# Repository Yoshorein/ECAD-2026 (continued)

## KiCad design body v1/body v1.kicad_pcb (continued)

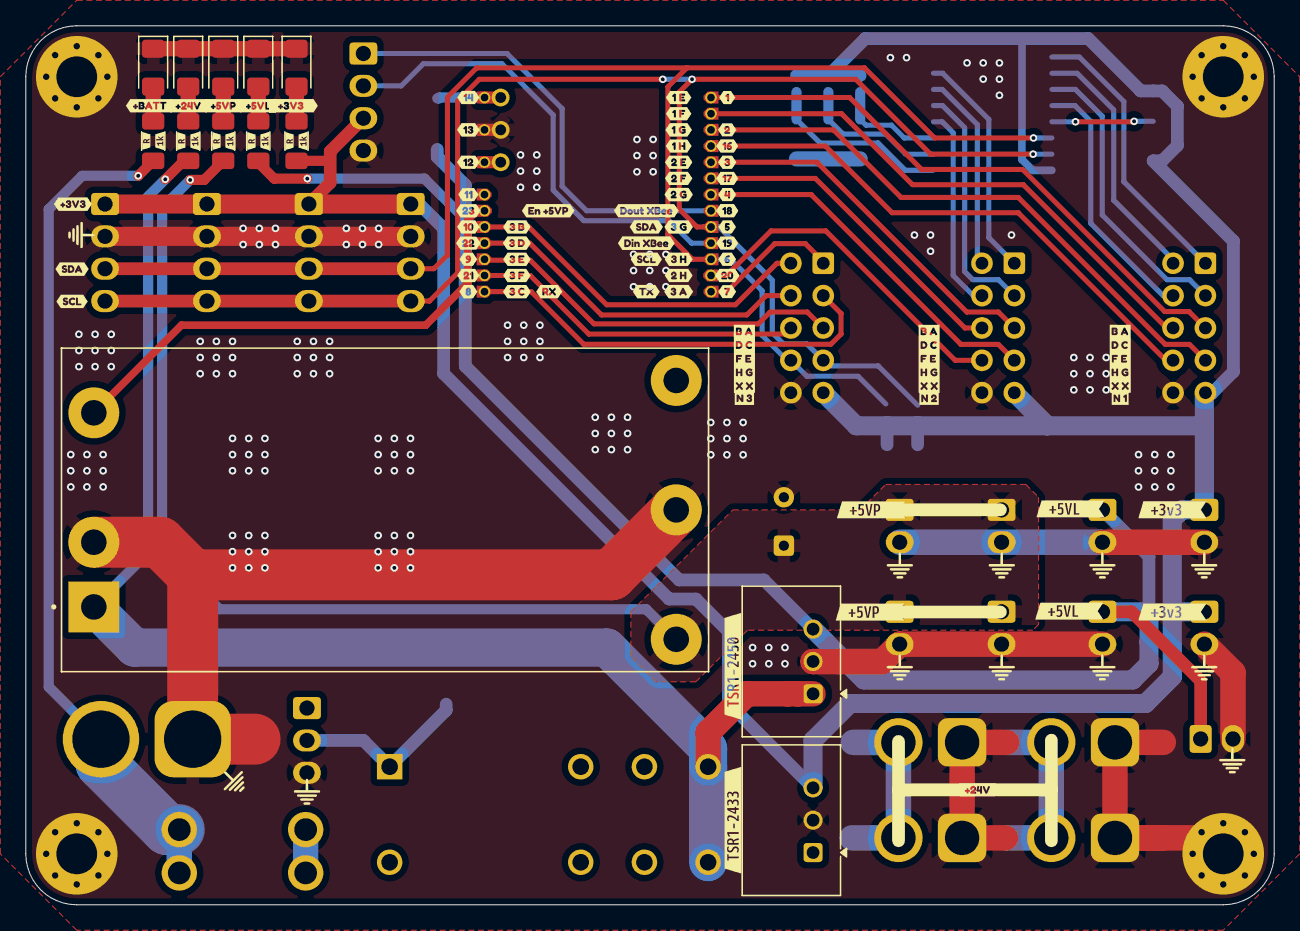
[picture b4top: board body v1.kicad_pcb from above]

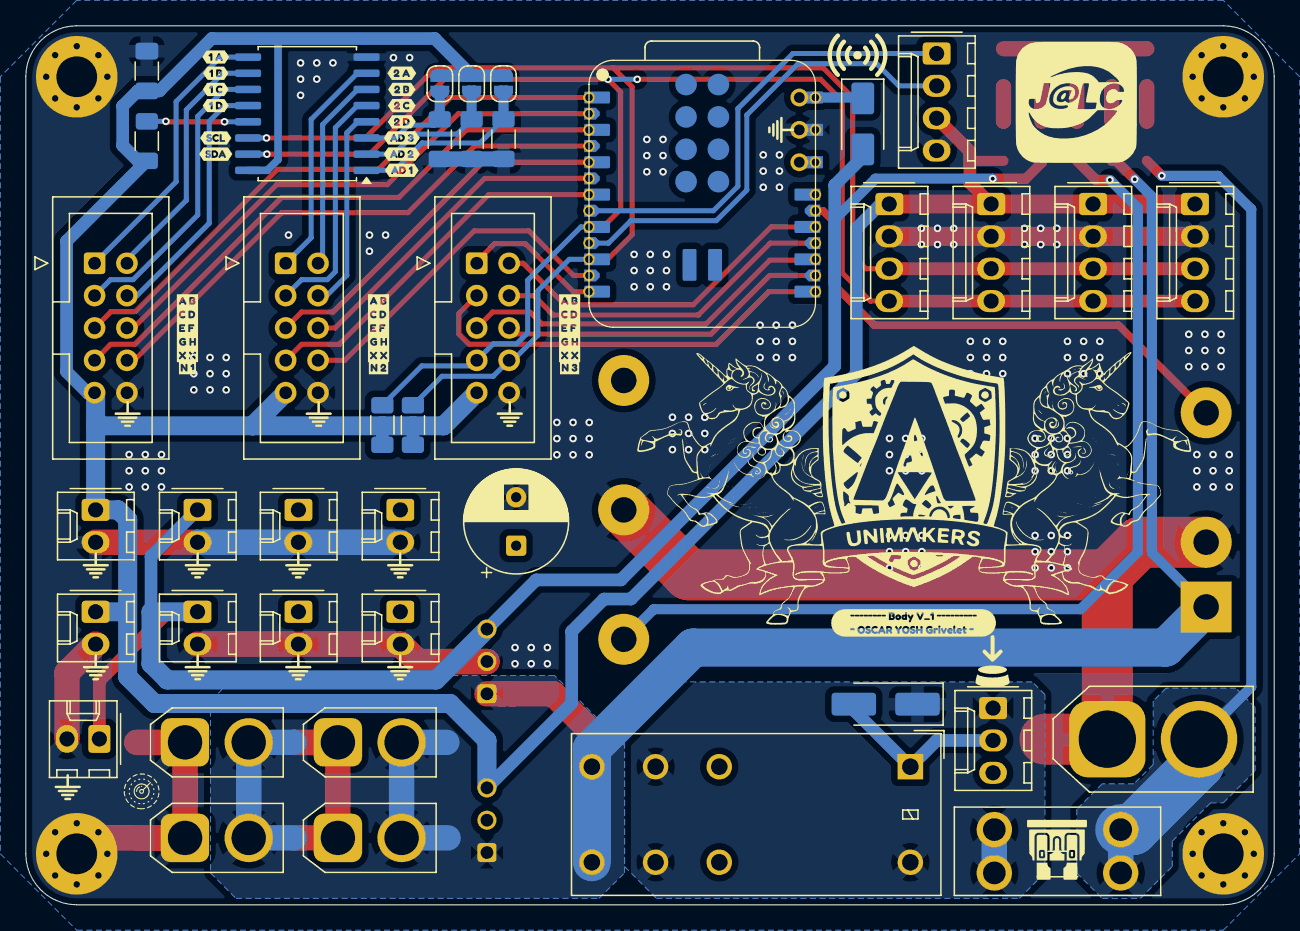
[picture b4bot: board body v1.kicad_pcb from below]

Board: 2 copper layers, 98.0 x 69.0 mm, 155 parts (60 on the bottom side), 45 nets.

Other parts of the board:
kibuzzard-69B7FC1F: G***; kibuzzard-69B7FC1F
kibuzzard-69B7FC2C: G***; kibuzzard-69B7FC2C
kibuzzard-69B7FC3A: G***; kibuzzard-69B7FC3A
kibuzzard-69B7FC3F: G***; kibuzzard-69B7FC3F
kibuzzard-69B7FC4C: G***; kibuzzard-69B7FC4C
kibuzzard-69B7FC5D: G***; kibuzzard-69B7FC5D
kibuzzard-69B7FC6B: G***; kibuzzard-69B7FC6B
kibuzzard-69B7FC8A: G***; kibuzzard-69B7FC8A
kibuzzard-69B7FC8F: G***; kibuzzard-69B7FC8F
kibuzzard-69B7FC9A: G***; kibuzzard-69B7FC9A
kibuzzard-69B7FC16: G***; kibuzzard-69B7FC16
kibuzzard-69B7FC28: G***; kibuzzard-69B7FC28
kibuzzard-69B7FC30: G***; kibuzzard-69B7FC30
kibuzzard-69B7FC34: G***; kibuzzard-69B7FC34
kibuzzard-69B7FC45: G***; kibuzzard-69B7FC45
kibuzzard-69B7FC49: G***; kibuzzard-69B7FC49
kibuzzard-69B7FC50: G***; kibuzzard-69B7FC50
kibuzzard-69B7FC58: G***; kibuzzard-69B7FC58
kibuzzard-69B7FC64: G***; kibuzzard-69B7FC64
kibuzzard-69B7FC71: G***; kibuzzard-69B7FC71
kibuzzard-69B7FC84: G***; kibuzzard-69B7FC84
kibuzzard-69B7FC95: G***; kibuzzard-69B7FC95
kibuzzard-69B7FF7A: G***; kibuzzard-69B7FF7A
kibuzzard-69B7FF72: G***; kibuzzard-69B7FF72
kibuzzard-69B7FFCA: G***; kibuzzard-69B7FFCA
kibuzzard-69B800EA, kibuzzard-69B800EA#2: G***; kibuzzard-69B800EA
kibuzzard-69B80110, kibuzzard-69B80110#2: G***; kibuzzard-69B80110
kibuzzard-69B80117, kibuzzard-69B80117#2: G***; kibuzzard-69B80117
kibuzzard-69BAE0CF: G***; kibuzzard-69BAE0CF
kibuzzard-69BAE4CB: G***; kibuzzard-69BAE4CB
kibuzzard-69BAE4D9: G***; kibuzzard-69BAE4D9
kibuzzard-69BAE4E7: G***; kibuzzard-69BAE4E7
kibuzzard-69BAE4F1: G***; kibuzzard-69BAE4F1
kibuzzard-69BAE7DC: G***; kibuzzard-69BAE7DC
kibuzzard-69BAE8DD, kibuzzard-69BAE8DD#2, kibuzzard-69BAE8DD#3: G***; kibuzzard-69BAE8DD
kibuzzard-69BAE35E: G***; kibuzzard-69BAE35E
kibuzzard-69BAE38F: G***; kibuzzard-69BAE38F
kibuzzard-69BAE48B: G***; kibuzzard-69BAE48B
kibuzzard-69BAE75D, kibuzzard-69BAE75D#2, kibuzzard-69BAE75D#3: G***; kibuzzard-69BAE75D
kibuzzard-69BAE77A: G***; kibuzzard-69BAE77A
kibuzzard-69BAE350: G***; kibuzzard-69BAE350
kibuzzard-69BAE367: G***; kibuzzard-69BAE367
kibuzzard-69BAE380: G***; kibuzzard-69BAE380
kibuzzard-69BAE387: G***; kibuzzard-69BAE387
kibuzzard-69BAE395: G***; kibuzzard-69BAE395
kibuzzard-69BAE431: G***; kibuzzard-69BAE431
kibuzzard-69BAE443: G***; kibuzzard-69BAE443
kibuzzard-69BAE476: G***; kibuzzard-69BAE476
kibuzzard-69BAE766, kibuzzard-69BAE766#2, kibuzzard-69BAE766#3: G***; kibuzzard-69BAE766
kibuzzard-69BAE772: G***; kibuzzard-69BAE772
kibuzzard-69BAE799: G***; kibuzzard-69BAE799
kibuzzard-69BAE836: G***; kibuzzard-69BAE836
kibuzzard-69BAED5C: G***; kibuzzard-69BAED5C
kibuzzard-69BAED6C: G***; kibuzzard-69BAED6C
kibuzzard-69BAED73: G***; kibuzzard-69BAED73
kibuzzard-69BAED80: G***; kibuzzard-69BAED80
kibuzzard-69BAEDC3: G***; kibuzzard-69BAEDC3
kibuzzard-69BAEDD0: G***; kibuzzard-69BAEDD0
kibuzzard-69BAEDD6: G***; kibuzzard-69BAEDD6
kibuzzard-69BAEDDC: G***; kibuzzard-69BAEDDC
kibuzzard-69BAEEA0: G***; kibuzzard-69BAEEA0
kibuzzard-69BAEEAC: G***; kibuzzard-69BAEEAC
kibuzzard-69BAEEB4: G***; kibuzzard-69BAEEB4
kibuzzard-69BAFB08: G***; kibuzzard-69BAFB08
kibuzzard-69BAFC5E: G***; kibuzzard-69BAFC5E
kibuzzard-69BAFC53: G***; kibuzzard-69BAFC53
kibuzzard-69BAFC58: G***; kibuzzard-69BAFC58
kibuzzard-69BAFC82: G***; kibuzzard-69BAFC82
kibuzzard-69BAFCAD: G***; kibuzzard-69BAFCAD
kibuzzard-69BAFD5E, kibuzzard-69BAFD5E#2: G***; kibuzzard-69BAFD5E
kibuzzard-69BAFE68: G***; kibuzzard-69BAFE68
kibuzzard-69BAFE76: G***; kibuzzard-69BAFE76
kibuzzard-69BAFF00: G***; kibuzzard-69BAFF00
kibuzzard-69BAFF06: G***; kibuzzard-69BAFF06
kibuzzard-69BBC5C3: G***; kibuzzard-69BBC5C3
kibuzzard-69BBC5E5: G***; kibuzzard-69BBC5E5
kibuzzard-69BCFD1C: G***; kibuzzard-69BCFD1C
kibuzzard-69C651A2: G***; kibuzzard-69C651A2
kibuzzard-690E943A, kibuzzard-690E943A#2, kibuzzard-690E943A#3, kibuzzard-690E943A#4, kibuzzard-690E943A#5: G***; kibuzzard-690E943A
kibuzzard-690E9406, kibuzzard-690E9406#2, kibuzzard-690E9406#3, kibuzzard-690E9406#4, kibuzzard-690E9406#5: G***; kibuzzard-690E9406

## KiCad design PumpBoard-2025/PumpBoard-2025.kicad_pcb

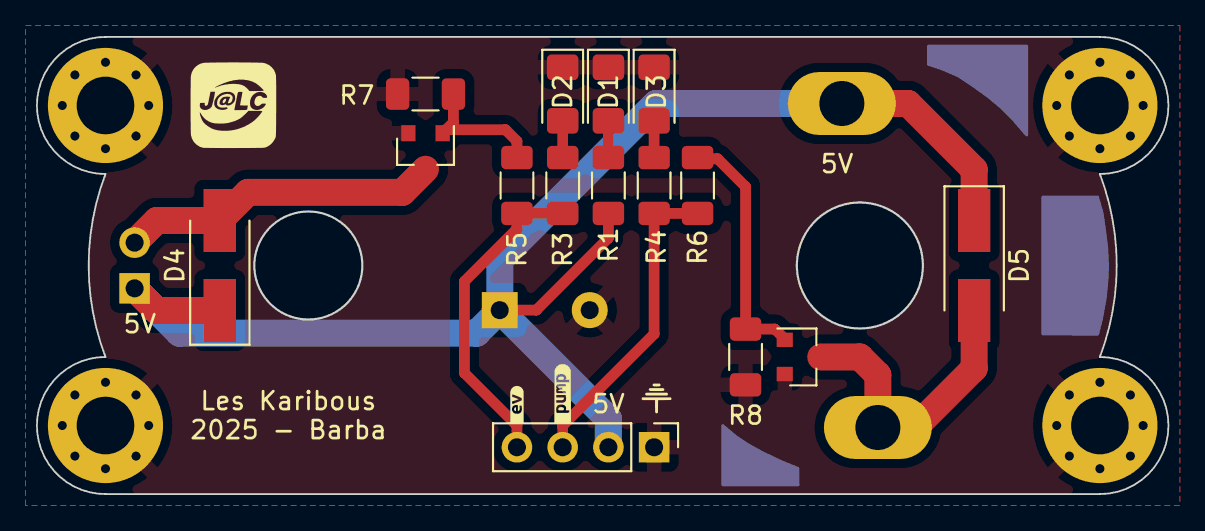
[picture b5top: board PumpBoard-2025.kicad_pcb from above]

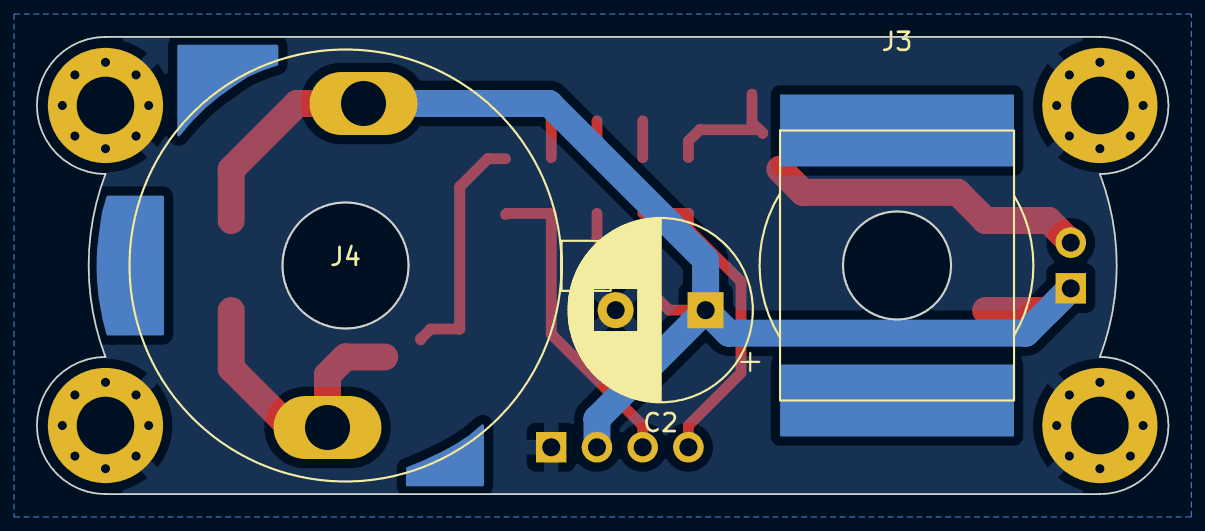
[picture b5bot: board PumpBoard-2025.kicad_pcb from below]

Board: 2 copper layers, 62.9 x 25.4 mm, 24 parts (3 on the bottom side), 11 nets.

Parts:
C2: C_Polarized_Small; CP_Radial_D10.0mm_P5.00mm
D1, D2, D3: LED_Small; LED_1206_3216Metric_Pad1.42x1.75mm_HandSolder
D4, D5: D_Small; D_SMA_Handsoldering
H1, H2, H3, H4: MountingHole_Pad; MountingHole_3.2mm_M3_Pad_Via
J1: Conn_01x04; PinHeader_1x04_P2.54mm_Vertical
J3: CON_EV; MiniEV
J4: CON_PUMP; motor-pump-370
Q1, Q2: AO3400A; SOT-23
R1, R3: 1K; R_1206_3216Metric_Pad1.30x1.75mm_HandSolder
R4: 1k; R_1206_3216Metric_Pad1.30x1.75mm_HandSolder
R5, R6: 270R; R_1206_3216Metric_Pad1.30x1.75mm_HandSolder
R7, R8: 10K; R_1206_3216Metric_Pad1.30x1.75mm_HandSolder
kibuzzard-67A8F3A7: G***; kibuzzard-67A8F3A7
kibuzzard-67A8F398: G***; kibuzzard-67A8F398

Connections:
+5V: C2.1, D4.1 (K), D5.1 (K), J1.2, J3.2, J4.1, R1.1
GND: C2.2, D1.1 (K), D2.1 (K), D3.1 (K), H1.1, H2.1, H3.1, H4.1, J1.1, Q1.2 (S), Q2.2 (S), R7.2, R8.2
unnamed: D1.2 (A), R1.2
unnamed: D2.2 (A), R3.2
unnamed: D3.2 (A), R4.2
unnamed: D4.2 (A), J3.1, Q1.3 (D)
unnamed: D5.2 (A), J4.2, Q2.3 (D)
unnamed: Q1.1 (G), R5.1, R7.1
unnamed: Q2.1 (G), R6.2, R8.1
S_EV: J1.4, R3.1, R5.2
S_PUMP: J1.3, R4.1, R6.1

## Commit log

2026-03-04 end schema body
2026-03-10 fin schema
2026-03-10 nique
2026-03-11 11/03
2026-03-13 routage body
2026-03-16 16/03
2026-03-18 debut dessin
2026-03-20 end of body +start of head
2026-03-23 head update
2026-03-23 fin routage head
2026-03-26 fin routage head manque que la serigraphie
2026-03-27 modif + carte pami ninja
2026-03-30 end head
2026-03-30 push for command
2026-03-30 order files
